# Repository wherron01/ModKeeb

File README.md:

# ModKeeb
A completely modular ortholinear keyboard comprised of solder-together 1u PCBs

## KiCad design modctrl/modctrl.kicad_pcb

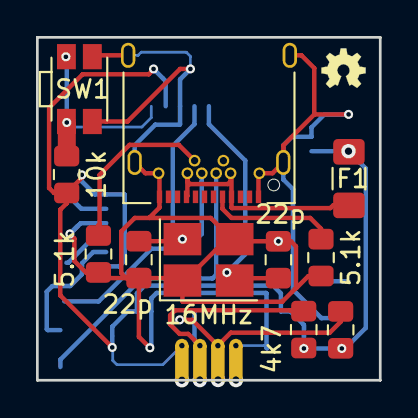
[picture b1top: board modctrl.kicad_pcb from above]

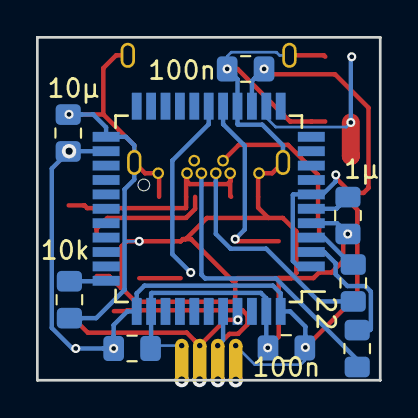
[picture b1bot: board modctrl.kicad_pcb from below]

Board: 2 copper layers, 19.0 x 19.0 mm, 21 parts (9 on the bottom side), 16 nets.

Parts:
C1: 100nF; C_0805_2012Metric_Pad1.15x1.40mm_HandSolder
C2, C3: 22p; C_0805_2012Metric_Pad1.15x1.40mm_HandSolder
C4, C5: 100n; C_0805_2012Metric_Pad1.15x1.40mm_HandSolder
C6: 10μ; C_0805_2012Metric_Pad1.15x1.40mm_HandSolder
C7: 1μ; C_0805_2012Metric_Pad1.15x1.40mm_HandSolder
F1: Polyfuse; Fuse_1206_3216Metric_Pad1.42x1.75mm_HandSolder
J1: USB_C_Receptacle; USB_C_Receptacle_Amphenol_12401548E4-2A
J2: Conn_01x04; edgeconnector
R1, R2: 5.1k; R_0805_2012Metric_Pad1.15x1.40mm_HandSolder
R3: 22; R_0805_2012Metric_Pad1.15x1.40mm_HandSolder
R4: 22Ω; R_0805_2012Metric_Pad1.15x1.40mm_HandSolder
R5, R6: 10k; R_0805_2012Metric_Pad1.15x1.40mm_HandSolder
R7, R8: 4k7; R_0805_2012Metric_Pad1.15x1.40mm_HandSolder
SW1: SW_Push; SW_SPST_EVQP7A
U1: ATmega32U4-AU; TQFP-44_10x10mm_P0.8mm
Y1: 16MHz; Crystal_SMD_3225-4Pin_3.2x2.5mm_HandSoldering

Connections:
+5V: C1.1, C4.1, C5.1, C6.1, F1.1, J2.1, R5.1, R7.1, R8.1, U1.2, U1.7, U1.14, U1.24, U1.34, U1.44
/CC1: J1.A5, R1.2
/CC2: J1.B5, R2.2
/Cry1: C3.1, U1.17, Y1.2
/Cry2: C2.1, U1.16, Y1.4
/HWB: R6.2, U1.33
/RES: R5.2, SW1.2, U1.13
/UDN: J1.A7, J1.B7, R3.2
/UDP: J1.A6, J1.B6, R4.2
/Ucap: C7.1, U1.6
/VCC: F1.2, J1.A4, J1.A9, J1.B4, J1.B9
D+: R4.1, U1.4
D-: R3.1, U1.3
GND: C1.2, C2.2, C3.2, C4.2, C5.2, C6.2, C7.2, J1.A1, J1.A12, J1.B1, J1.B12, J1.S1, J2.4, R1.1, R2.1, R6.1, SW1.1, U1.5, U1.15, U1.23, U1.35, U1.43, Y1.1, Y1.3
SCL: J2.3, R8.2, U1.41
SDA: J2.2, R7.2, U1.40

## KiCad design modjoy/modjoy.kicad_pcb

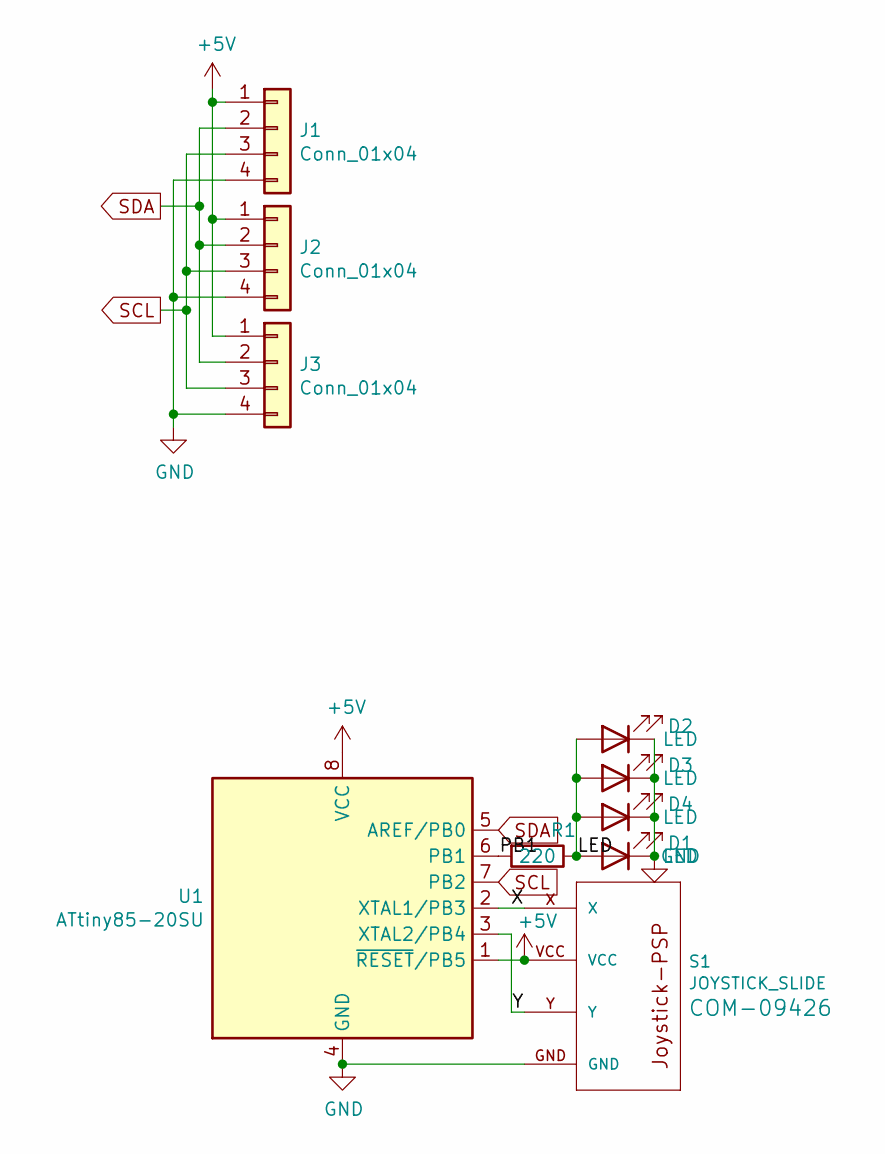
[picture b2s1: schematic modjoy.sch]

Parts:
D1, D2, D3, D4: LED; LED_0805_2012Metric_Pad1.15x1.40mm_HandSolder
J1, J2, J3: Conn_01x04; edgeconnector
R1: 220; R_0805_2012Metric_Pad1.15x1.40mm_HandSolder
S1: JOYSTICK_SLIDE; JOYSTICK-PSP1000-noscrew
U1: ATtiny85-20SU; SOIJ-8_5.3x5.3mm_P1.27mm

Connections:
+5V: J1.1, J2.1, J3.1, S1.VCC, U1.1 (~RESET~/PB5), U1.8 (VCC)
/LED: D1.2 (A), D2.2 (A), D3.2 (A), D4.2 (A), R1.1
/PB1: R1.2, U1.6 (PB1)
/X: S1.X, U1.2 (XTAL1/PB3)
/Y: S1.Y, U1.3 (XTAL2/PB4)
GND: D1.1 (K), D2.1 (K), D3.1 (K), D4.1 (K), J1.4, J2.4, J3.4, S1.GND, U1.4 (GND)
SCL: J1.3, J2.3, J3.3, U1.7 (PB2)
SDA: J1.2, J2.2, J3.2, U1.5 (AREF/PB0)

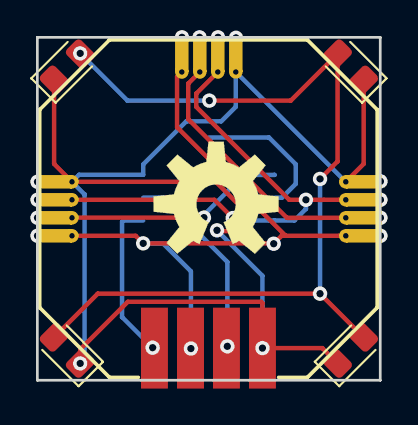
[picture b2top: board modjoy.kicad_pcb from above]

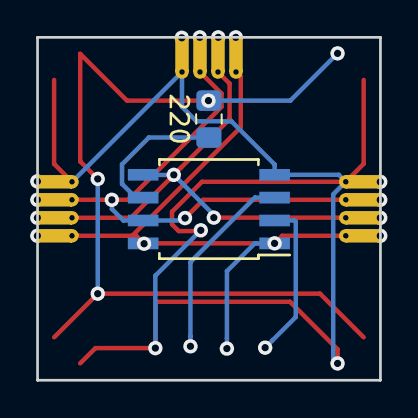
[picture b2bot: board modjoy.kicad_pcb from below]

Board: 2 copper layers, 19.1 x 19.0 mm, 10 parts (4 on the bottom side), 8 nets.

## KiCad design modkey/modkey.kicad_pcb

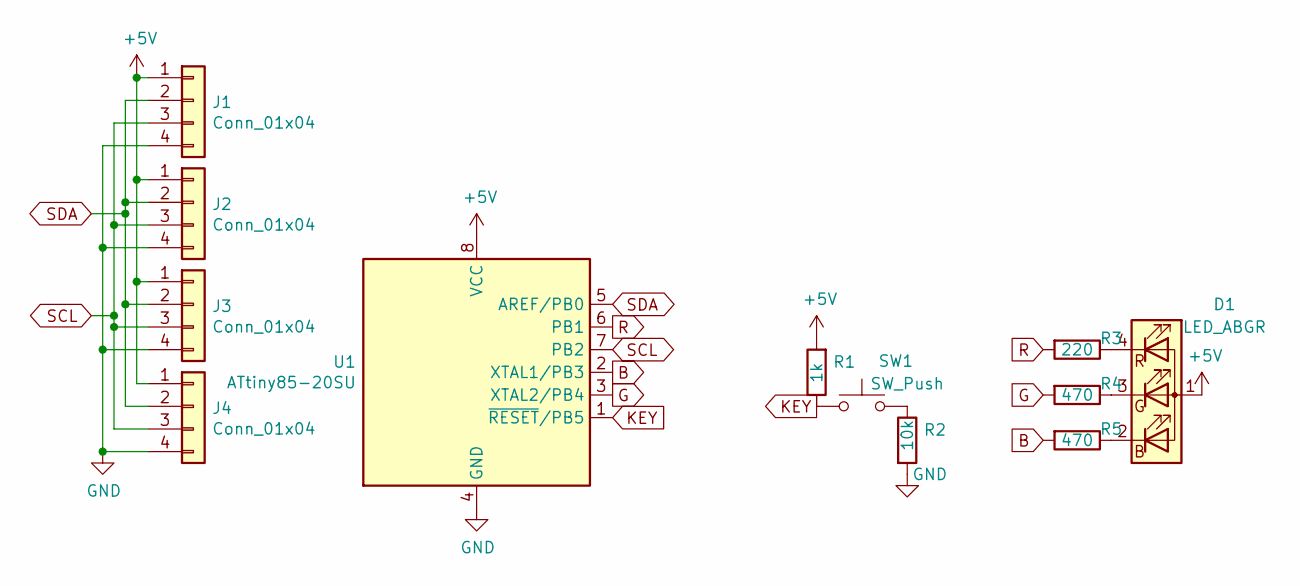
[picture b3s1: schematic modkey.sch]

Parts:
D1: LED_ABGR; LED_Cree-PLCC4_2x2mm_CW
J1, J2, J3, J4: Conn_01x04; edgeconnector
R1: 1k; R_0805_2012Metric_Pad1.20x1.40mm_HandSolder
R2: 10k; R_0805_2012Metric_Pad1.20x1.40mm_HandSolder
R3: 220; R_0805_2012Metric_Pad1.15x1.40mm_HandSolder
R4, R5: 470; R_0805_2012Metric_Pad1.15x1.40mm_HandSolder
SW1: SW_Push; MX-Alps-Choc-X-1U-NoLED
U1: ATtiny85-20SU; SOIJ-8_5.3x5.3mm_P1.27mm

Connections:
+5V: D1.1 (A), J1.1, J2.1, J3.1, J4.1, R1.2, U1.8 (VCC)
B: R5.2, U1.2 (XTAL1/PB3)
G: R4.2, U1.3 (XTAL2/PB4)
GND: J1.4, J2.4, J3.4, J4.4, R2.2, U1.4 (GND)
KEY: R1.1, SW1.1, U1.1 (~RESET~/PB5)
unnamed: D1.2 (BK), R5.1
unnamed: D1.3 (GK), R4.1
unnamed: D1.4 (RK), R3.1
unnamed: R2.1, SW1.2
R: R3.2, U1.6 (PB1)
SCL: J1.3, J2.3, J3.3, J4.3, U1.7 (PB2)
SDA: J1.2, J2.2, J3.2, J4.2, U1.5 (AREF/PB0)

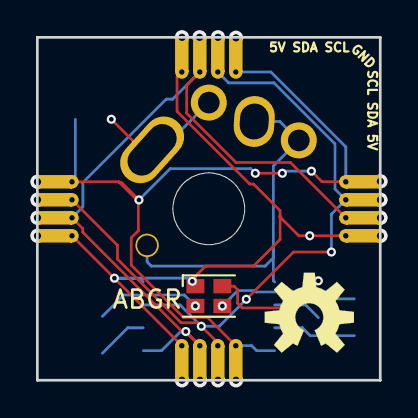
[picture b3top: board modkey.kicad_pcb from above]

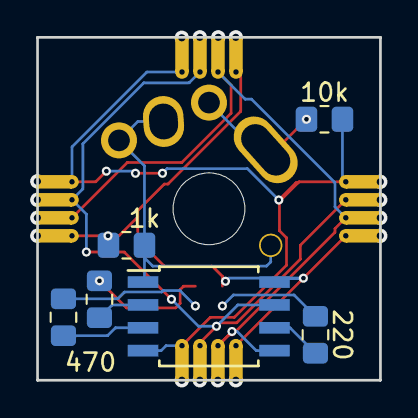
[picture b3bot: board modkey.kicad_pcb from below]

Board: 2 copper layers, 19.1 x 19.0 mm, 12 parts (8 on the bottom side), 12 nets.

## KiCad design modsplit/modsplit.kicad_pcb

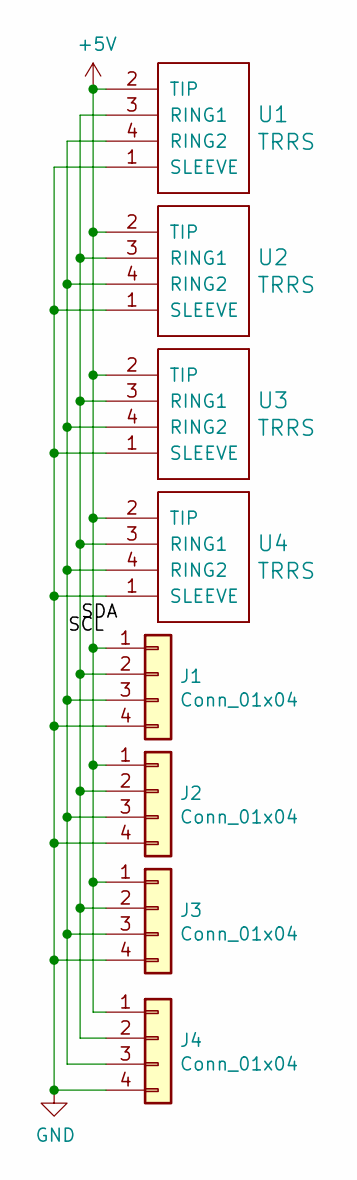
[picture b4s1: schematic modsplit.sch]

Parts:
J1, J2, J3, J4: Conn_01x04; edgeconnector
U1, U2, U3, U4: TRRS; TRRS-PJ-320D

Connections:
+5V: J1.1, J2.1, J3.1, J4.1, U1.2 (TIP), U2.2 (TIP), U3.2 (TIP), U4.2 (TIP)
/SCL: J1.3, J2.3, J3.3, J4.3, U1.4 (RING2), U2.4 (RING2), U3.4 (RING2), U4.4 (RING2)
/SDA: J1.2, J2.2, J3.2, J4.2, U1.3 (RING1), U2.3 (RING1), U3.3 (RING1), U4.3 (RING1)
GND: J1.4, J2.4, J3.4, J4.4, U1.1 (SLEEVE), U2.1 (SLEEVE), U3.1 (SLEEVE), U4.1 (SLEEVE)

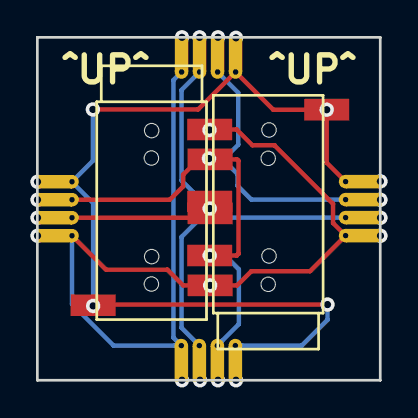
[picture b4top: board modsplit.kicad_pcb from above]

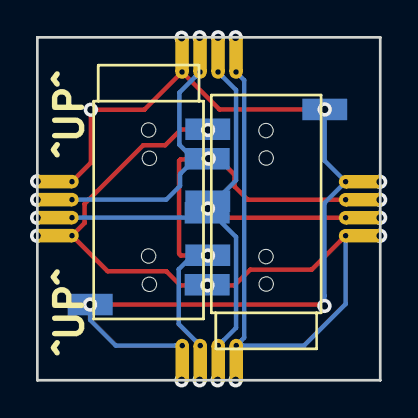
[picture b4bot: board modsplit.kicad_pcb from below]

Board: 2 copper layers, 19.0 x 19.0 mm, 8 parts (4 on the bottom side), 4 nets.

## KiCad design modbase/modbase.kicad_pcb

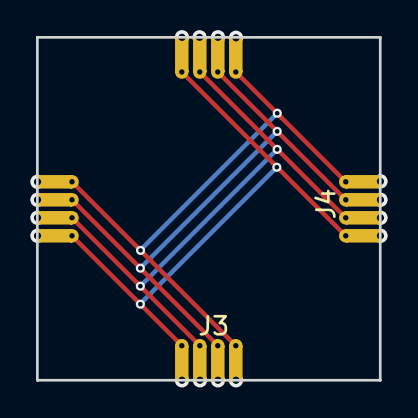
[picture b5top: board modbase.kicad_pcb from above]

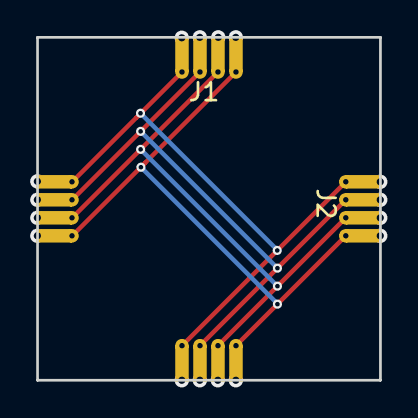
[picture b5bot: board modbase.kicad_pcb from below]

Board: 2 copper layers, 19.1 x 19.0 mm, 4 parts (2 on the bottom side), 4 nets.

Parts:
J1, J2, J3, J4: Conn_01x04; edgeconnector

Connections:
+5V: J1.1, J2.1, J3.1, J4.1
GND: J1.4, J2.4, J3.4, J4.4
SCL: J1.3, J2.3, J3.3, J4.3
SDA: J1.2, J2.2, J3.2, J4.2

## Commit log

2020-02-04 enough dicking around
2020-02-04 pull up with less than the force of a thousand suns
2020-02-09 Added blank and joystick modules
2021-07-03 cleanup
